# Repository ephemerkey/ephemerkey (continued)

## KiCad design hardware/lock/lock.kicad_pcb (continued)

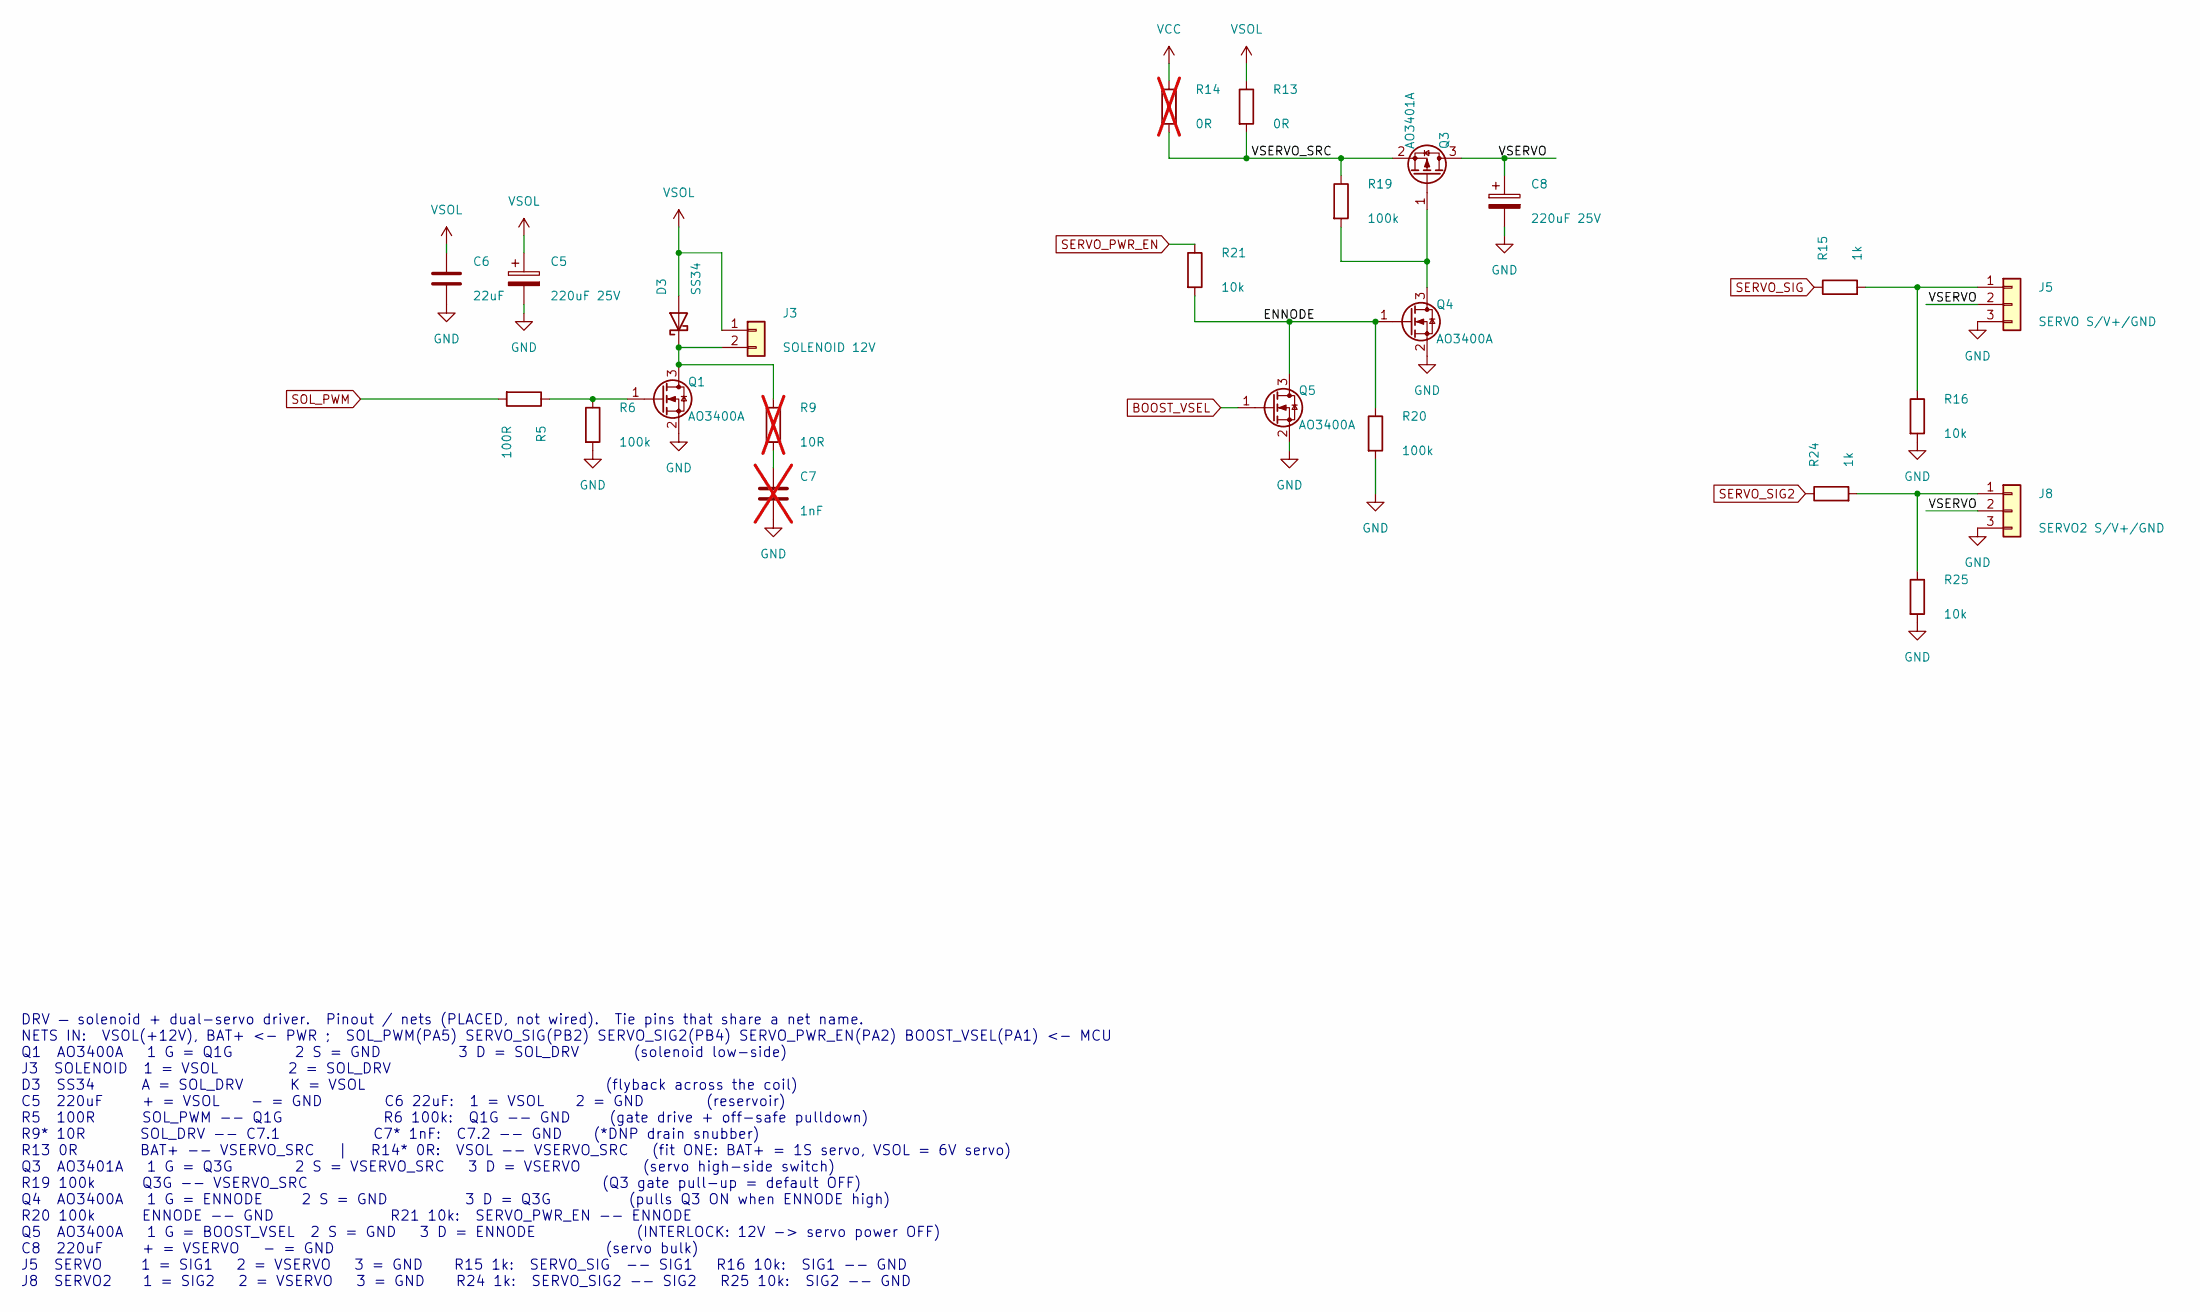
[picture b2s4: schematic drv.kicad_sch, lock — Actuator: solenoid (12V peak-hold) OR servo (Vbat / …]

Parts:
C5, C8: 220uF 25V; CP_Elec_6.3x7.7; MPN RVT1E221M0607; LCSC C2918361
C6: 22uF; C_1206_3216Metric; LCSC C12891
C7: 1nF; C_0402_1005Metric; not fitted
D3: SS34; D_SMA; MPN SS34; LCSC C8678
J3: SOLENOID 12V; JST_PH_S2B-PH-K_1x02_P2.00mm_Horizontal; MPN S2B-PH-K-S; LCSC C173752
J5: SERVO S/V+/GND; PinHeader_1x03_P2.54mm_Vertical
J8: SERVO2 S/V+/GND; PinHeader_1x03_P2.54mm_Vertical
Q1, Q4, Q5: AO3400A; SOT-23; MPN AO3400A; LCSC C20917
Q3: AO3401A; SOT-23; MPN AO3401A; LCSC C15127
R5: 100R; R_0402_1005Metric; LCSC C106232
R6, R19, R20: 100k; R_0402_1005Metric; LCSC C25741
R9: 10R; R_0402_1005Metric; not fitted
R13: 0R; R_0402_1005Metric; LCSC C17168
R14: 0R; R_0402_1005Metric; LCSC C17168; not fitted
R15, R24: 1k; R_0402_1005Metric; LCSC C11702
R16, R21, R25: 10k; R_0402_1005Metric; LCSC C25744

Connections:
/DRV/ENNODE: Q4.1 (G), Q5.3 (D), R20.1, R21.2
/DRV/VSERVO: C8.1, J5.2, J8.2, Q3.3 (D)
/DRV/VSERVO_SRC: Q3.2 (S), R13.2, R14.2, R19.1
BOOST_VSEL: Q5.1 (G); also elsewhere on the board
GND: C5.2, C6.2, C7.2, C8.2, J5.3, J8.3, Q1.2 (S), Q4.2 (S), Q5.2 (S), R6.2, R16.2, R20.2, R25.2; also elsewhere on the board
unnamed: C7.1, R9.2
unnamed: D3.1 (K), J3.2, Q1.3 (D), R9.1
unnamed: J5.1, R15.2, R16.1
unnamed: J8.1, R24.2, R25.1
unnamed: Q1.1 (G), R5.1, R6.1
unnamed: Q3.1 (G), Q4.3 (D), R19.2
SERVO_PWR_EN: R21.1; also elsewhere on the board
SERVO_SIG: R15.1; also elsewhere on the board
SERVO_SIG2: R24.1; also elsewhere on the board
SOL_PWM: R5.2; also elsewhere on the board
VCC: R14.1; also elsewhere on the board
VSOL: C5.1, C6.1, D3.2 (A), J3.1, R13.1; also elsewhere on the board

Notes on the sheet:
DRV — solenoid + dual-servo driver. Pinout / nets (PLACED, not wired). Tie pins that share a net name. NETS IN: VSOL(+12V), BAT+ <- PWR ; SOL_PWM(PA5) SERVO_SIG(PB2) SERVO_SIG2(PB4) SERVO_PWR_EN(PA2) BOOST_VSEL(PA1) <- MCU Q1 AO3400A 1 G = Q1G 2 S = GND 3 D = SOL_DRV (solenoid low-side) J3 SOLENOID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

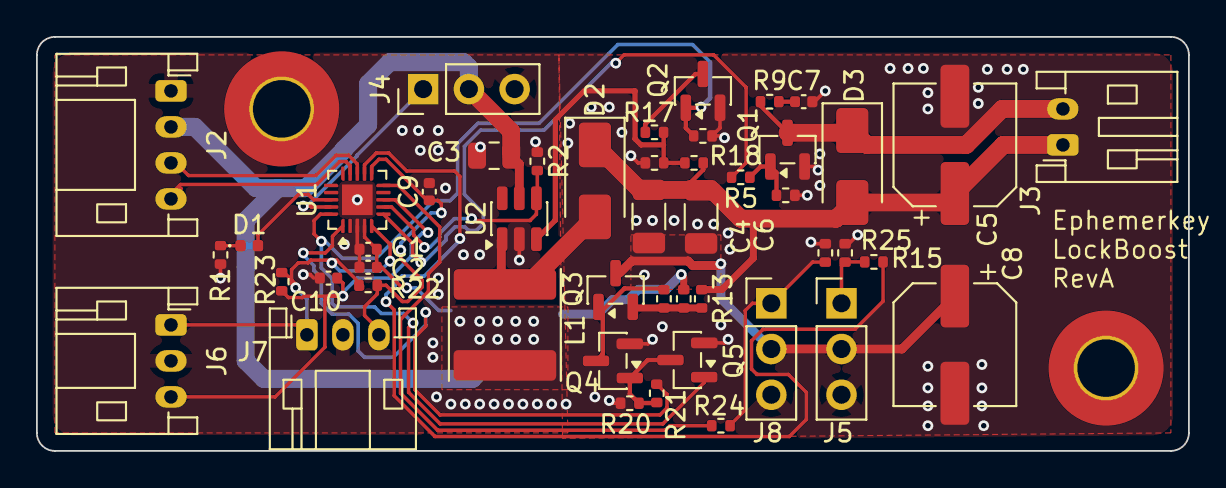
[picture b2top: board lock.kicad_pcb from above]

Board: 2 copper layers, 64.0 x 23.0 mm, 50 parts (0 on the bottom side), 29 nets.

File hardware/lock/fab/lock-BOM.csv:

"Item","Designator","Comment","Footprint","Qty","LCSC Part #","MPN","Manufacturer"
"1","C1,C9,C10","100nF","Capacitor_SMD:C_0402_1005Metric","3","C1525","",""
"2","C2","1uF","Capacitor_SMD:C_0402_1005Metric","1","C29266","",""
"3","C3","10uF","Capacitor_SMD:C_0805_2012Metric","1","C15850","",""
"4","C4,C6","22uF","Capacitor_SMD:C_1206_3216Metric","2","C12891","",""
"5","C5,C8","220uF 25V","Capacitor_SMD:CP_Elec_6.3x7.7","2","C2918361","RVT1E221M0607","Rubycon-alt"
"6","D1","STAT","LED_SMD:LED_0402_1005Metric","1","C160479","LTST-C281KGKT","Lite-On"
"7","D2,D3","SS34","Diode_SMD:D_SMA","2","C8678","SS34","MDD"
"8","J2","I2C JST-PH RA","Connector_JST:JST_PH_S4B-PH-K_1x04_P2.00mm_Horizontal","1","C157926","S4B-PH-K-S","JST"
"9","J3","SOLENOID 12V","Connector_JST:JST_PH_S2B-PH-K_1x02_P2.00mm_Horizontal","1","C173752","S2B-PH-K-S","JST"
"10","J4","UPDI PROG","Connector_PinHeader_2.54mm:PinHeader_1x03_P2.54mm_Vertical","1","","",""
"11","J5","SERVO S/V+/GND","Connector_PinHeader_2.54mm:PinHeader_1x03_P2.54mm_Vertical","1","","",""
"12","J6","HALL DOOR","Connector_JST:JST_PH_S3B-PH-K_1x03_P2.00mm_Horizontal","1","C157929","S3B-PH-K-S","JST"
"13","J7","HALL BOLT","Connector_JST:JST_PH_S3B-PH-K_1x03_P2.00mm_Horizontal","1","C157929","S3B-PH-K-S","JST"
"14","J8","SERVO2 S/V+/GND","Connector_PinHeader_2.54mm:PinHeader_1x03_P2.54mm_Vertical","1","","",""
"15","L1","10uH","Inductor_SMD:L_Changjiang_FNR6045S","1","C168076","FNR6045S100MT","Changjiang"
"16","Q1,Q2,Q4,Q5","AO3400A","Package_TO_SOT_SMD:SOT-23","4","C20917","AO3400A","AOS"
"17","Q3","AO3401A","Package_TO_SOT_SMD:SOT-23","1","C15127","AO3401A","AOS"
"18","R1,R15,R24","1k","Resistor_SMD:R_0402_1005Metric","3","C11702","",""
"19","R2,R6,R18-R20","100k","Resistor_SMD:R_0402_1005Metric","5","C25741","",""
"20","R3","200k","Resistor_SMD:R_0402_1005Metric","1","C25764","",""
"21","R4","22k","Resistor_SMD:R_0402_1005Metric","1","C25768","",""
"22","R5","100R","Resistor_SMD:R_0402_1005Metric","1","C106232","",""
"23","R13","0R","Resistor_SMD:R_0402_1005Metric","1","C17168","",""
"24","R16,R21-R23,R25","10k","Resistor_SMD:R_0402_1005Metric","5","C25744","",""
"25","R17","20k","Resistor_SMD:R_0402_1005Metric","1","C25765","",""
"26","U1","ATtiny1616","Package_DFN_QFN:VQFN-20-1EP_3x3mm_P0.4mm_EP1.7x1.7mm","1","C507118","ATTINY1616-MNR","Microchip"
"27","U2","MT3608","Package_TO_SOT_SMD:SOT-23-6","1","C84817","MT3608","Aerosemi"

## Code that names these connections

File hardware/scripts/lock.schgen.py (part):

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(shared secret in MCU flash -- no secure element), and drives a 12 V solenoid
with a firmware peak-and-hold (economizer) profile.  It has NO local battery:
VCC + the boost/actuator draw are fed from ephemerkey's VSYS rail over J2.2 (the
I2C connector).  J1 removed.  Status LED (D1) is driven by PC3.

Power architecture (chosen for "off most of the time, draw as little as
possible"):
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MCU["note"] = (12, 140, """MCU — ATtiny1616 (QFN-20) controller.  Pinout / nets (PLACED, not wired).  Runs off BAT, no LDO.
 pin name        net                              pin name   net
  4 VCC          BAT+  (C1, C2 to GND)             3 GND      GND  (+ EP pin 21)
 19 PA0/RESET    UPDI = J4.1                        5 PA4      HALL_PWR -> J6.1, J7.1, R22, R23
 14 PB0 SCL      = J2.4   (I2C clk + wake)          6 PA5      SOL_PWM -> DRV R5
 13 PB1 SDA      = J2.3   (I2C data)                7 PA6      SOL_BOOST_EN -> PWR U2.EN
 18 PC3          LED: PC3 -> D1 -> R1 -> GND        8 PB2      SERVO_SIG  -> DRV R15
  2 PA3          spare (unused -> add NC flag)
 20 PA1          BOOST_VSEL -> PWR Q2 + DRV Q5      1 PA2      SERVO_PWR_EN -> DRV R21
  8 PA7          HALL_DOOR  <- J6.3                11 PB3      HALL_BOLT  <- J7.3
                 PB4  SERVO_SIG2 -> DRV R24            spare:  PB5, PC0, PC1, PC2, PC3
PASSIVES:  C1 100nF VCC--GND    C2 1uF VCC--GND    D1 LED + R1 1k:  PC3 -- D1 -- R1 -- GND
J2 I2C   (S4B-PH-K 4-pin):  1 = GND   2 = VCC <- ephemerkey VSYS (power in)   3 = SDA (PB1)   4 = SCL (PB0)
J4 UPDI  (1x3 header):      1 = UPDI (PA0)   2 = VCC (BAT)   3 = GND
J6 HALL DOOR (S3B 3-pin):   1 = HALL_PWR   2 = GND   3 = OUT -> PA7 ;  R22 10k OUT--HALL_PWR ;  C9  100nF OUT--GND
J7 HALL BOLT (S3B 3-pin):   1 = HALL_PWR   2 = GND   3 = OUT -> PB3 ;  R23 10k OUT--HALL_PWR ;  C10 100nF OUT--GND""")

PWR["note"] = (12, 120, """PWR — power-in (VSYS via J2) + MT3608 boost.  Pinout / nets (hand-wired; see KiCad).
POWER IN:  VCC (= ephemerkey VSYS) arrives on J2.2 (MCU sheet) -> feeds U2 IN + U1/MCU + DRV.  No local battery (J1 removed).
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R17 20k     FB -- Q2.D                              (switched in -> 12V)
Q2 AO3400   1 G = BOOST_VSEL   2 S = GND   3 D = R17    (FB switch: 6V <-> 12V)
R2 100k     U2.EN -- GND                            R18 100k:  BOOST_VSEL -- GND   (default OFF / 6V)
NETS IN:  U2.EN <- SOL_BOOST_EN (PA6) ;  BOOST_VSEL <- PA1.    OUT:  BAT+, VSOL -> DRV.
Vout = 0.6*(1 + R3/Rbot):  Rbot = R4 -> 6V ;  R4 || R17 (Q2 on) -> 12V.""")

DRV["note"] = (12, 95, """DRV — solenoid + dual-servo driver.  Pinout / nets (PLACED, not wired).  Tie pins that share a net name.
NETS IN:  VSOL(+12V), BAT+ <- PWR ;  SOL_PWM(PA5) SERVO_SIG(PB2) SERVO_SIG2(PB4) SERVO_PWR_EN(PA2) BOOST_VSEL(PA1) <- MCU
Q1  AO3400A   1 G = Q1G        2 S = GND          3 D = SOL_DRV       (solenoid low-side)
J3  SOLENOID  1 = VSOL         2 = SOL_DRV
D3  SS34      A = SOL_DRV      K = VSOL                               (flyback across the coil)
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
